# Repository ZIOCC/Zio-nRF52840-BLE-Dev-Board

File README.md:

## Zio nRF52840 BLE Dev Board

> This board is available for purchase [here](https://www.smart-prototyping.com/Zio-Qwiic-nrf52840-Dev-Board)

This is a development and breakout board based on nRF52840 SoC - a powerful combination of ARM Cortex-M4 CPU and 2.4GHz Bluetooth radio. With the nRF52840 at the heart of your project, you’ll be presented with a seemingly endless list of project-possibilities in an incredibly small package.

This board breaks out most of the nRF52840 module’s pins, including GPIO, UART, SPI, I2C, NFC, etc.. With the Micro USB connector, you can easily program and supply power to it. We’ve flashed [Adafruit’s nrf52 bootloader](https://github.com/adafruit/Adafruit_nRF52_Bootloader), an Arduino core for our nRF board, so you can interface with the arduino IDE. 

Additionally, we put a Qwiic connector on the board, so you can easily use our Qwiic modules with this development board. And there is a [full-color addressable LED WS2812-2020](https://www.smart-prototyping.com/WS2812-2020-Addressable-Fullcolor-RGB-LED) connected to Pin8. We also break out the NFC pins for NFC testing purpose. 

It also support programming with CircuitPython, check sparkfun’s tutorial [here](https://learn.sparkfun.com/tutorials/sparkfun-pro-nrf52840-mini-hookup-guide). 

You can find most of the technical specifications details from the [nRF52840 module datasheet](https://github.com/ZIOCC/Zio-nRF52840-BLE-Dev-Board/blob/master/MDBT50Q-P.pdf). 

**Other Specifications**

* Dimension: 57.4 x 23.9mm
* Weight: 5.1g
* Operation Voltage: 3.3V

**Links**

* [PCB schematic](https://github.com/ZIOCC/Zio-nRF52840-BLE-Dev-Board/blob/master/zio%20nRF52840%20BLE%20Dev%20Board.pdf)
* [PCB Source File](https://github.com/ZIOCC/Zio-nRF52840-BLE-Dev-Board/tree/master/EAGLE)
* [Datasheet](https://github.com/ZIOCC/Zio-nRF52840-BLE-Dev-Board/blob/master/MDBT50Q-P.pdf) 
* [Nordic nRF5 SDK](https://www.nordicsemi.com/eng/Products/Bluetooth-low-energy/nRF5-SDK) 
* [Bootloader Source Code](https://github.com/adafruit/Adafruit_nRF52_Bootloader)
* [Adafruit Arduino IDE tutorial](https://learn.adafruit.com/introducing-the-adafruit-nrf52840-feather)
* [Sparkfun CircuitPython tutorial](https://learn.sparkfun.com/tutorials/sparkfun-pro-nrf52840-mini-hookup-guide)
* [Pins definition](https://www.smart-prototyping.com/image/data/NOA-RnD/101968%20nrf52840%20dev%20board/nRF52840_variant.h)
* [GitHub](https://github.com/ZIOCC/Zio-nRF52840-BLE-Dev-Board)

###### About Zio
> Zio is a new line of open sourced, compact, and grid layout boards, fully integrated for Arduino and Qwiic ecosystem. Designed ideally for wearables, robotics, small-space limitations or other on the go projects. Check out other awesome Zio products [here](https://www.smart-prototyping.com/Zio).

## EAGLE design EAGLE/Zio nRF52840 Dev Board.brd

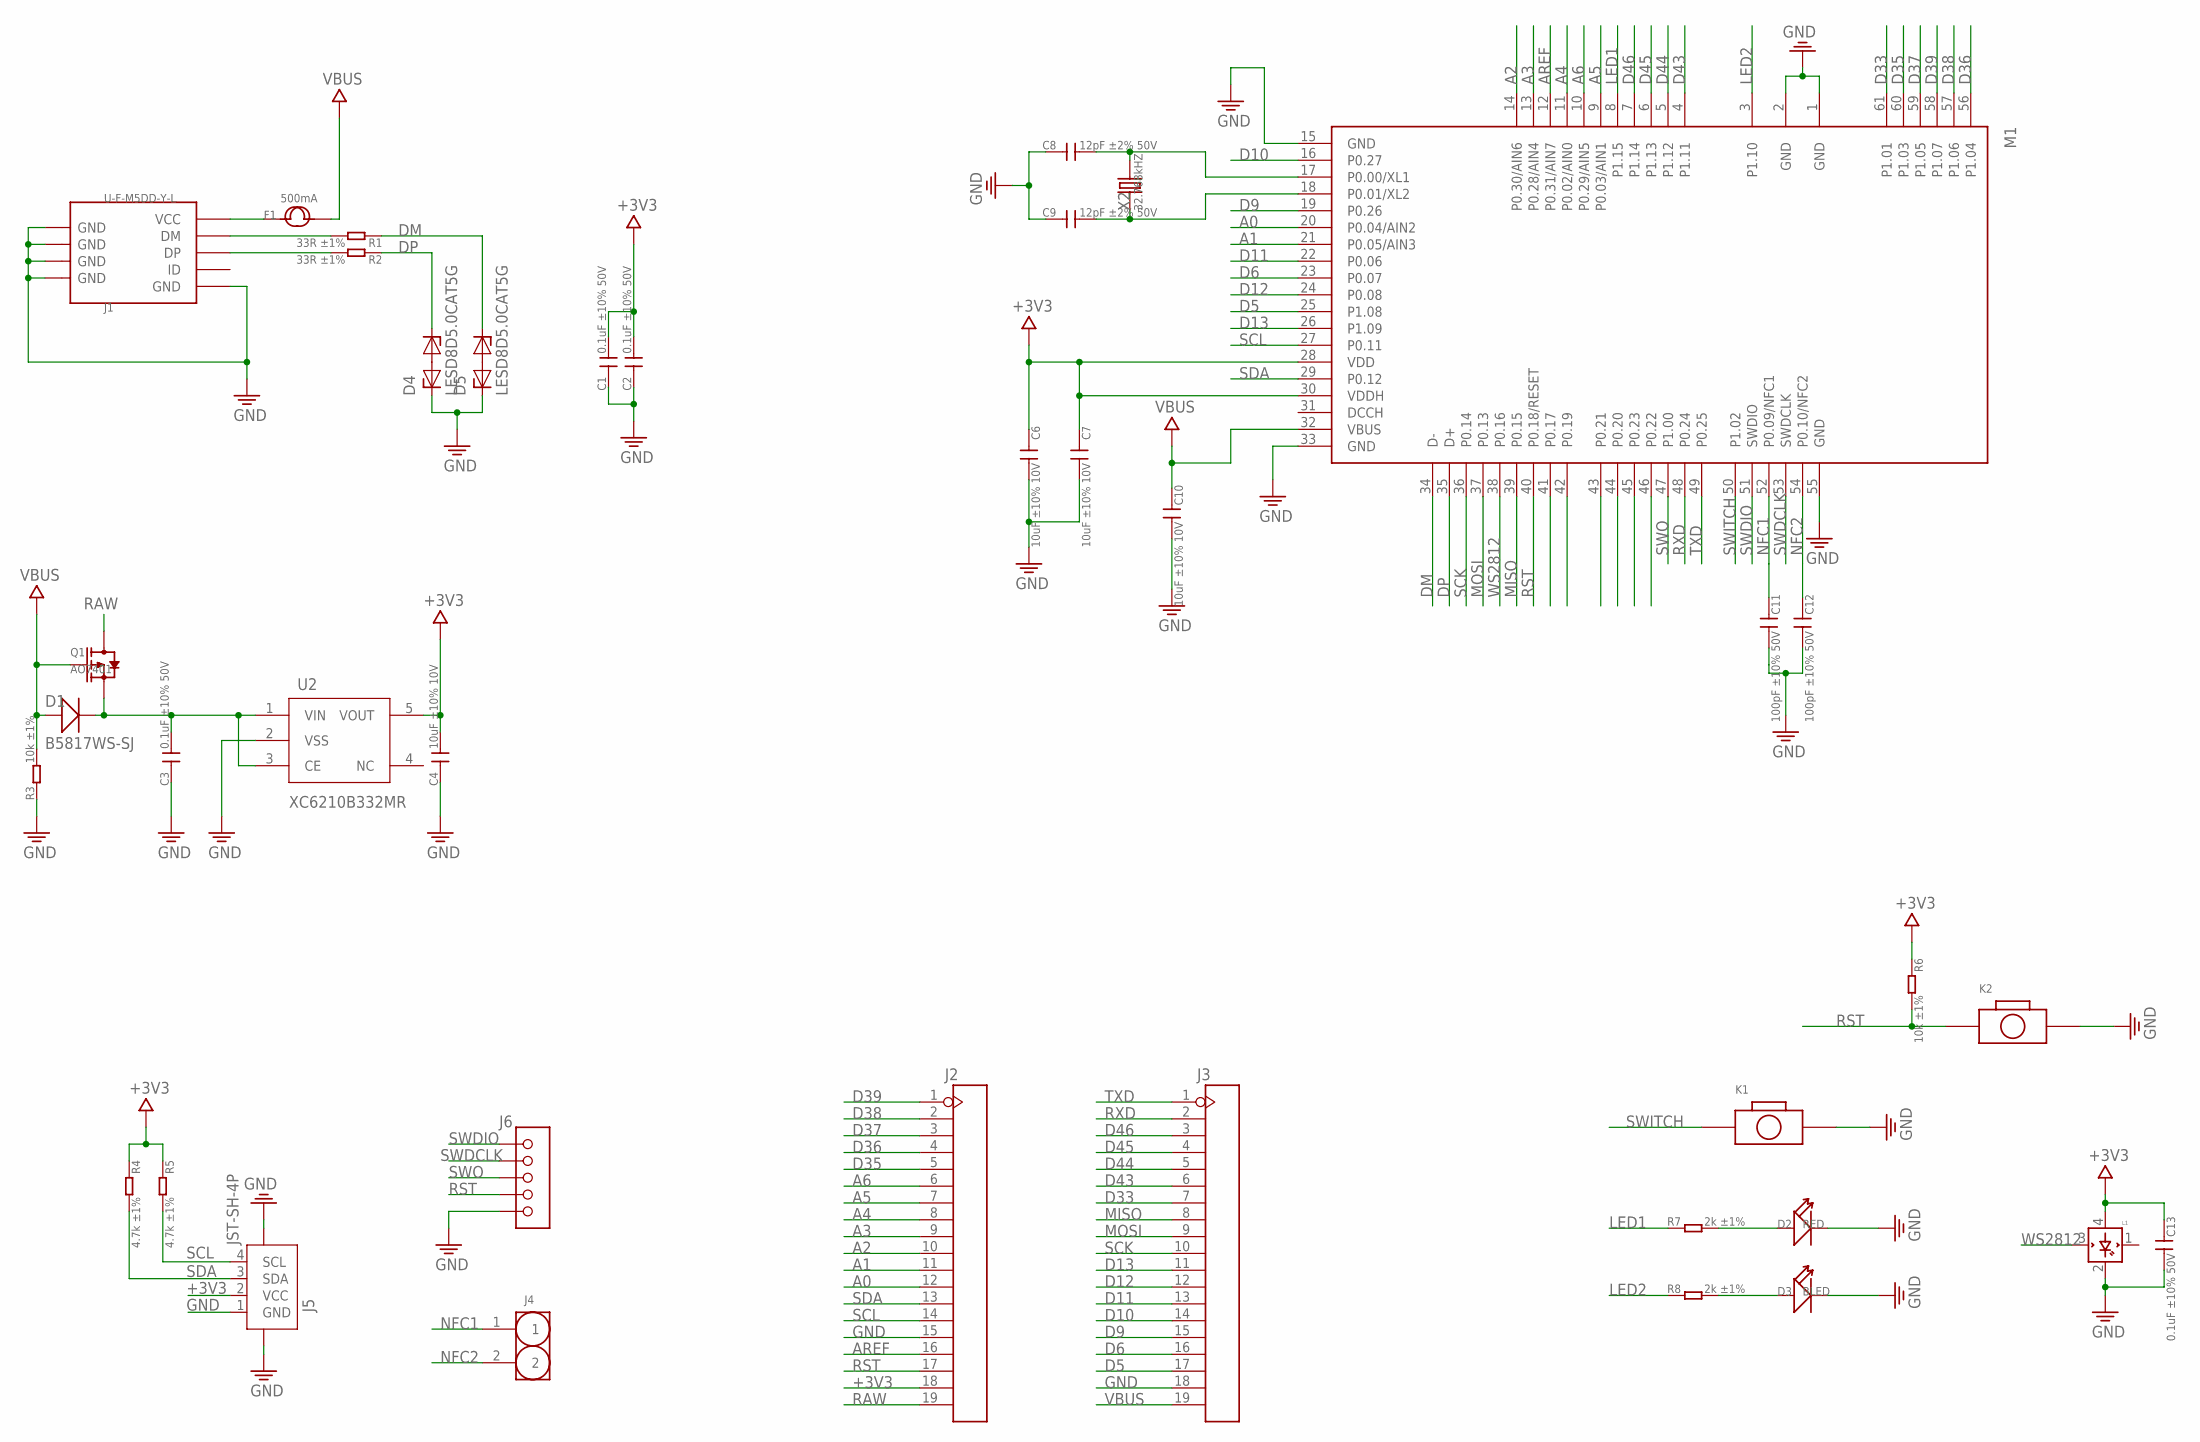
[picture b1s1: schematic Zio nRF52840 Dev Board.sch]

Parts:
C1, C2, C3, C13: 0.1uF ±10% 50V; C0402
C4, C6, C7, C10: 10uF ±10% 10V; C0603
C8, C9: 12pF ±2% 50V; C0402
C11, C12: 100pF ±10% 50V; C0402
D1: B5817WS-SJ; SOD323
D2: RED; LED-0603
D3: BLED; LED-0603
D4, D5: LESD8D5.0CAT5G; SOD882
F1: 500mA; 1206
J1: U-F-M5DD-Y-L; MICRO-SMD
J2, J3: HEADER-19P; 19P-2.54
J4: HEADER-2P-65/35MIL; 2P-2.54-65/35MIL
J5: JST-SH-4P; JST-SH-4P-90
J6: HEADER-5P-2.54; 5P-2.54
K1, K2: BOTTON-2PSKRKAEE020; SKRKAEE020
L1: WS2812B2020; WS2812_2020
M1: MDBT50
Q1: AO7401; SOT-323
R1, R2: 33R ±1%; R0402
R3, R6: 10k ±1%; R0402
R4, R5: 4.7k ±1%; R0402
R7, R8: 2k ±1%; R0402
U2: XC6210B332MR; SOT23-5
X2: 32.768kHZ; 2P-SMD-3.2X1.5

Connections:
+3V3: C1.2, C2.2, C4.2, C6.1, C7.1, C13.1, J2.18, J5.2 (VCC), L1.4 (VDD), M1.28 (VDD), M1.30 (VDDH), R4.1, R5.1, R6.1, U2.5 (VOUT)
A0: J2.12, M1.20 (P0.04/AIN2)
A1: J2.11, M1.21 (P0.05/AIN3)
A2: J2.10, M1.14 (P0.30/AIN6)
A3: J2.9, M1.13 (P0.28/AIN4)
A4: J2.8, M1.11 (P0.02/AIN0)
A5: J2.7, M1.9 (P0.03/AIN1)
A6: J2.6, M1.10 (P0.29/AIN5)
AREF: J2.16, M1.12 (P0.31/AIN7)
D5: J3.17, M1.25 (P1.08)
D6: J3.16, M1.23 (P0.07)
D9: J3.15, M1.19 (P0.26)
D10: J3.14, M1.16 (P0.27)
D11: J3.13, M1.22 (P0.06)
D12: J3.12, M1.24 (P0.08)
D13: J3.11, M1.26 (P1.09)
D33: J3.7, M1.61 (P1.01)
D35: J2.5, M1.60 (P1.03)
D36: J2.4, M1.56 (P1.04)
D37: J2.3, M1.59 (P1.05)
D38: J2.2, M1.57 (P1.06)
D39: J2.1, M1.58 (P1.07)
D43: J3.6, M1.4 (P1.11)
D44: J3.5, M1.5 (P1.12)
D45: J3.4, M1.6 (P1.13)
D46: J3.3, M1.7 (P1.14)
DM: D5.2, M1.34 (D-), R1.1
DP: D4.2, M1.35 (D+), R2.1
GND: C1.1, C2.1, C3.1, C4.1, C6.2, C7.2, C8.1, C9.1, C10.2, C11.2, C12.2, C13.2, D2.-, D3.-, D4.1, D5.1, J1.P5 (GND), J1.S1 (GND), J1.S2 (GND), J1.S3 (GND), J1.S4 (GND), J2.15, J3.18, J5.1 (GND), J5.5, J5.6, J6.5, K1.2, K2.2, L1.2 (GND), M1.1 (GND), M1.2 (GND), M1.15 (GND), M1.33 (GND), M1.55 (GND), R3.1, U2.2 (VSS)
LED1: M1.8 (P1.15), R7.1
LED2: M1.3 (P1.10), R8.1
MISO: J3.8, M1.39 (P0.15)
MOSI: J3.9, M1.37 (P0.13)
unnamed: D3.+, R8.2
unnamed: J1.P2 (DM), R1.2
unnamed: D2.+, R7.2
unnamed: C8.2, M1.17 (P0.00/XL1), X2.2
unnamed: F1.1, J1.P1 (VCC)
unnamed: J1.P3 (DP), R2.2
unnamed: C9.2, M1.18 (P0.01/XL2), X2.1
NFC1: C11.1, J4.1, M1.52 (P0.09/NFC1)
NFC2: C12.1, J4.2, M1.54 (P0.10/NFC2)
QSPI_CS: M1.44 (P0.20)
QSPI_DATA0: M1.41 (P0.17)
QSPI_DATA1: M1.46 (P0.22)
QSPI_DATA2: M1.45 (P0.23)
QSPI_DATA3: M1.43 (P0.21)
QSPI_SCK: M1.42 (P0.19)
RAW: J2.19, Q1.3 (D)
RST: J2.17, J6.4, K2.1, M1.40 (P0.18/RESET), R6.2
RXD: J3.2, M1.48 (P0.24)
SCK: J3.10, M1.36 (P0.14)
SCL: J2.14, J5.4 (SCL), M1.27 (P0.11), R5.2
SDA: J2.13, J5.3 (SDA), M1.29 (P0.12), R4.2
SWDCLK: J6.2, M1.53 (SWDCLK)
SWDIO: J6.1, M1.51 (SWDIO)
SWITCH: K1.1, M1.50 (P1.02)
SWO: J6.3, M1.47 (P1.00)
TXD: J3.1, M1.49 (P0.25)
VBUS: C10.1, D1.+, F1.2, J3.19, M1.32 (VBUS), Q1.1 (G), R3.2
VIN: C3.2, D1.-, Q1.2 (S), U2.1 (VIN), U2.3 (CE)
WS2812: L1.3 (DIN), M1.38 (P0.16)

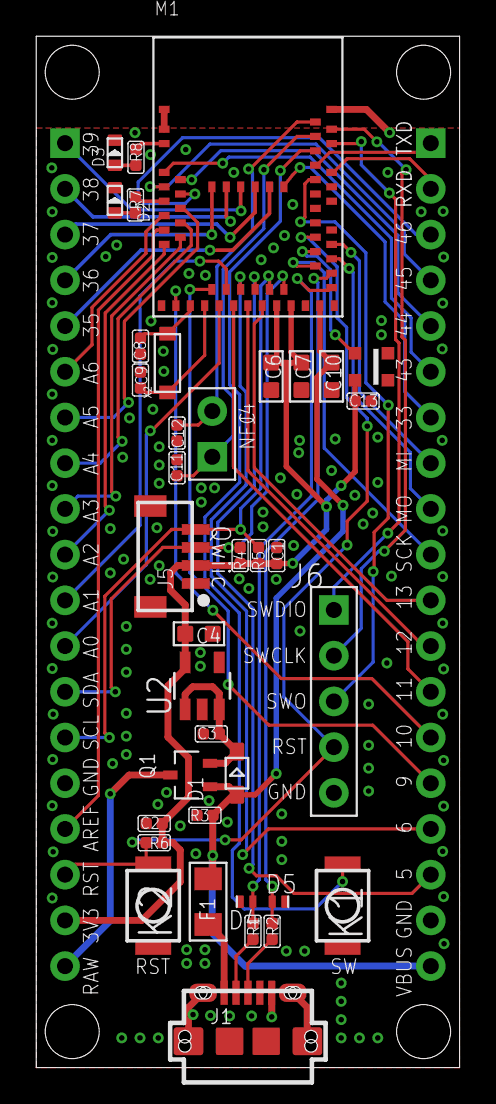
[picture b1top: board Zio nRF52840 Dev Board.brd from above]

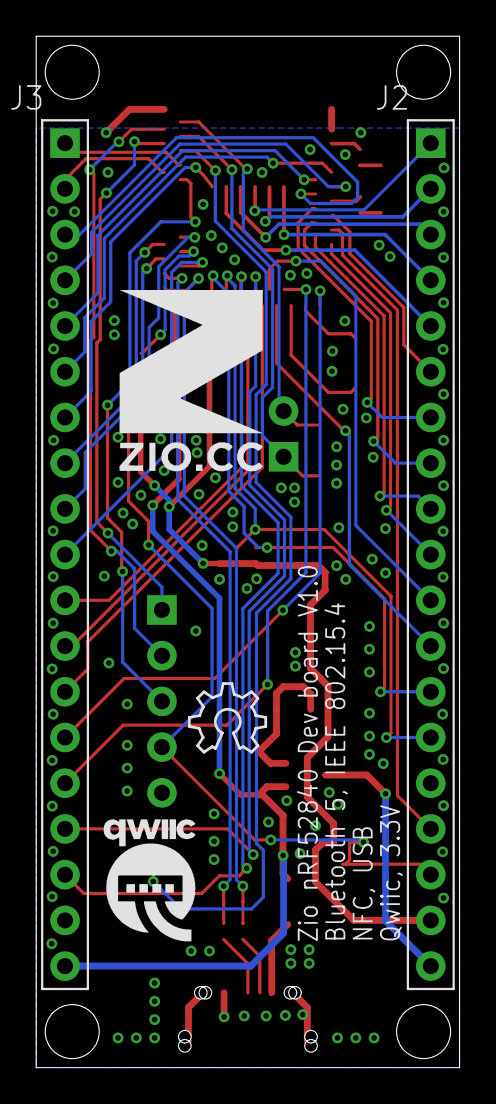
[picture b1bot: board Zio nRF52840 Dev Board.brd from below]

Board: 2 copper layers, 23.5 x 57.3 mm, 42 parts (5 on the bottom side), 56 nets.

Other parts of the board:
U$17: 10MM
U$18: QWIIC-LOGO-MEDIUM
U$19: OSHW_6X150_NOTEXT
